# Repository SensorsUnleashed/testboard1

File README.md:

# relayboard
Simple board that will be powered by both mains and a button cell battery.
It is able to:
* Operate a Single Pole Double Throw relay
* Connection for a [Optical Utility Meter LED Pulse Sensor](https://openenergymonitor.org/emon/opticalpulsesensor) from OpenEnergyMonitor
* Has a i2c eeprom
* Can attach to a Sensors Unleashed radio module
* If mains is lost, the relay will release, but the radio will still be operating. This means that messages can still be send even though power is removed.

This board has many uses, but some ideas could be:
Use any installation in the house as input for the system. This device will detect if a button has been toggled, and send messages as instructed. Perhaps turning on/off lamps or plugs in another location in a house.

The board has been ordered from DirtyPCBs 2016-12-05. When tested I will make sure to update this document.

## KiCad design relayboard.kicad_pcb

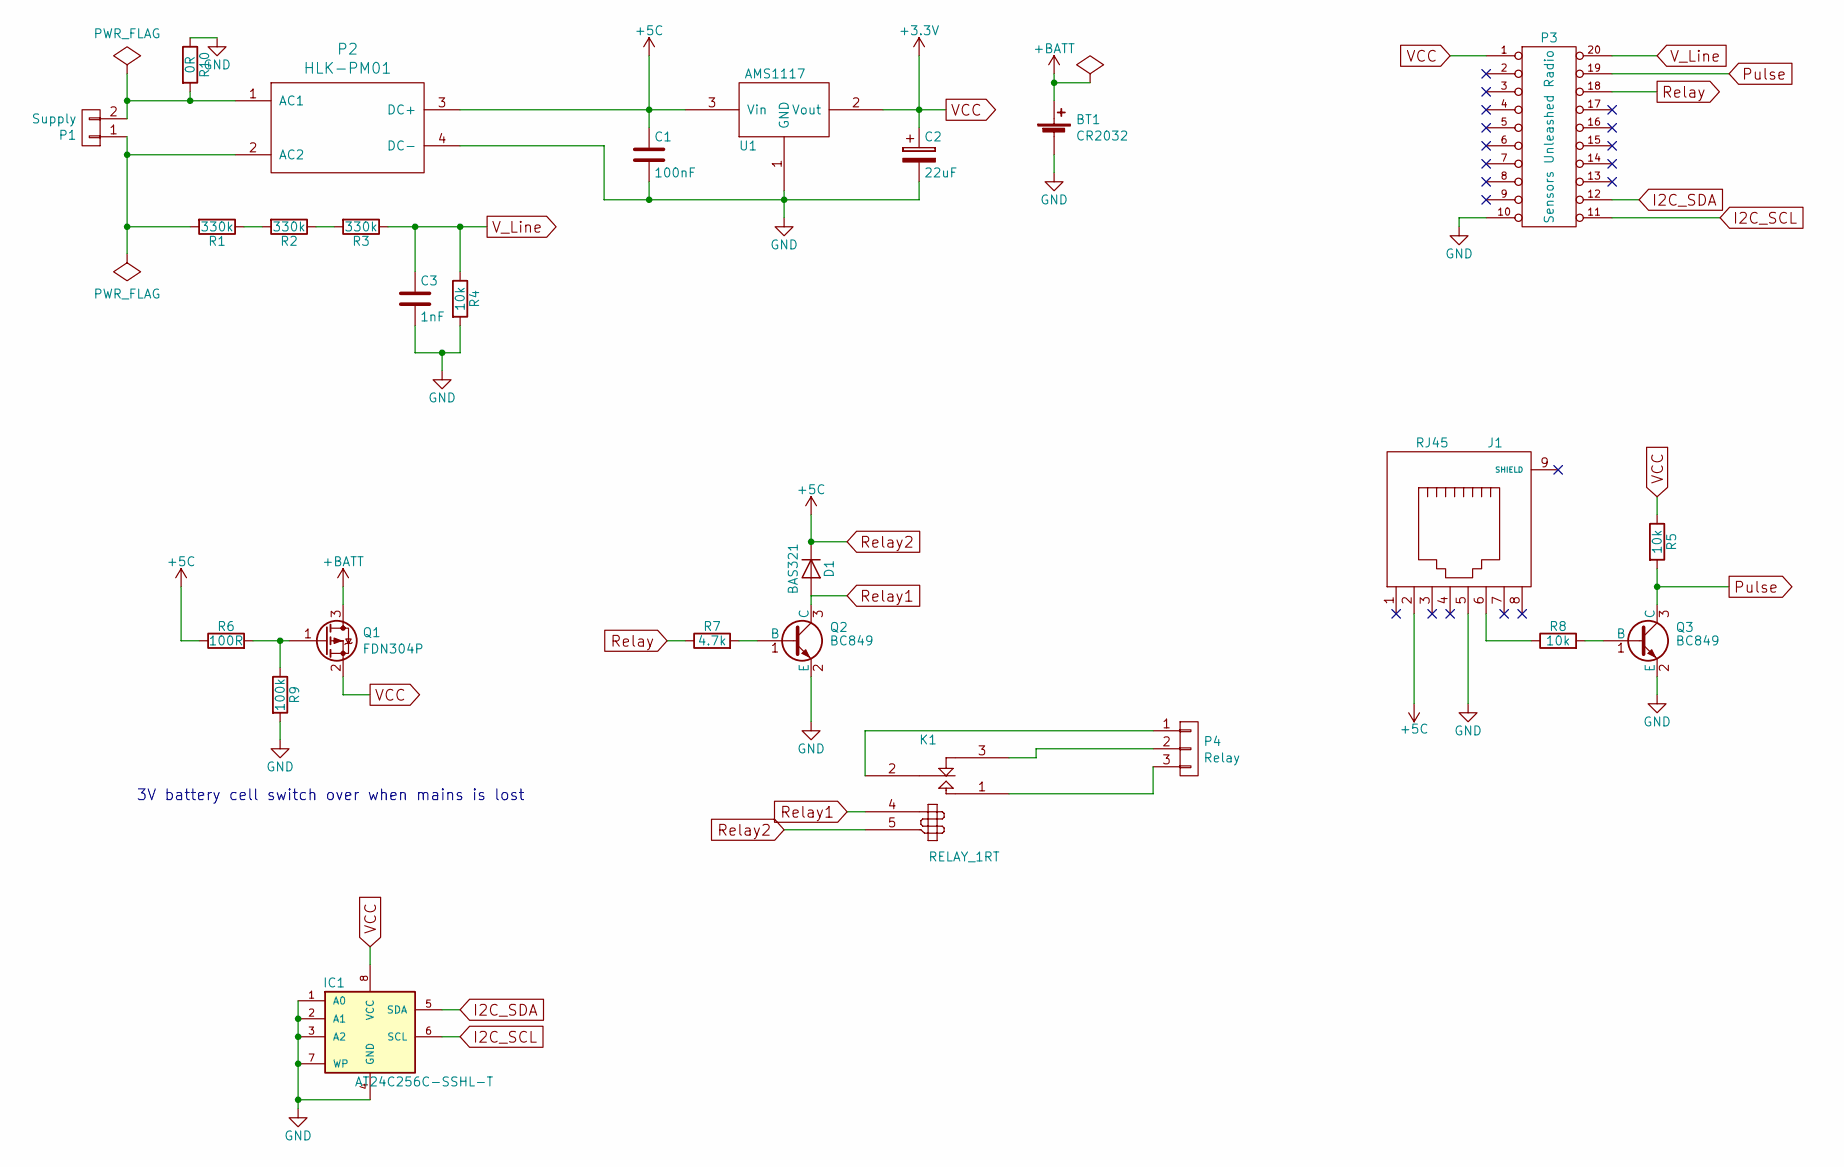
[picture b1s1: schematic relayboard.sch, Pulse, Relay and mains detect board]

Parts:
BT1: CR2032; BATT_CR2032_MPD; Manufacturer Part Number BC2032-F1
C1: 100nF; C_0805
C2: 22uF; C_0805; Manufacturer Part Number F981A226MSA
C3: 1nF; C_0805
D1: BAS321; SOD-323; Manufacturer Part Number BAS321,115
IC1: AT24C256C-SSHL-T; SOIC-8_3.9x4.9mm_Pitch1.27mm
J1: RJ45; RJ45_8
K1: RELAY_1RT; Relay_SRD_XVDC-SL-C_Series
P1: Supply; AK300-2
P2: HLK-PM01
P3: Sensors Unleashed Radio; zb3219PA_radio
P4: Relay; AK300-3
Q1: FDN304P; SSOT-3; Manufacturer Part Number FDN304P
Q2, Q3: BC849; SOT-23
R1, R2, R3: 330k; R_0805
R4, R5, R8: 10k; R_0805
R6: 100R; R_0805
R7: 4.7k; R_0805
R9: 100k; R_0805
R10: 0R; R_0805
U1: AMS1117; SOT-223; Manufacturer Part Number AMS1117-3.3

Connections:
+BATT: BT1.1 (+), Q1.3 (D)
GND: BT1.2 (-), C1.2, C2.2, C3.2, IC1.1 (A0), IC1.2 (A1), IC1.3 (A2), IC1.4 (GND), IC1.7 (WP), J1.5, P2.4 (DC-), P3.10, Q2.2 (E), Q3.2 (E), R4.2, R9.2, R10.1, U1.1 (GND)
I2C_SCL: IC1.6 (SCL), P3.11
I2C_SDA: IC1.5 (SDA), P3.12
unnamed: J1.6, R8.1
unnamed: K1.1 (T1), P4.3
unnamed: K1.2 (C1), P4.1
unnamed: K1.3 (R1), P4.2
unnamed: P1.1, P2.2 (AC2), R1.2
unnamed: P1.2, P2.1 (AC1), R10.2
unnamed: Q1.1 (G), R6.2, R9.1
unnamed: Q2.1 (B), R7.2
unnamed: Q3.1 (B), R8.2
unnamed: R1.1, R2.2
unnamed: R2.1, R3.2
Pulse: P3.19, Q3.3 (C), R5.2
Relay: P3.18, R7.1
Relay1: D1.2 (A), K1.4, Q2.3 (C)
Relay2: C1.1, D1.1 (K), J1.2, K1.5, P2.3 (DC+), R6.1, U1.3 (Vin)
VCC: C2.1, IC1.8 (VCC), P3.1, Q1.2 (S), R5.1, U1.2 (Vout)
V_Line: C3.1, P3.20, R3.1, R4.1

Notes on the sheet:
3V battery cell switch over when mains is lost

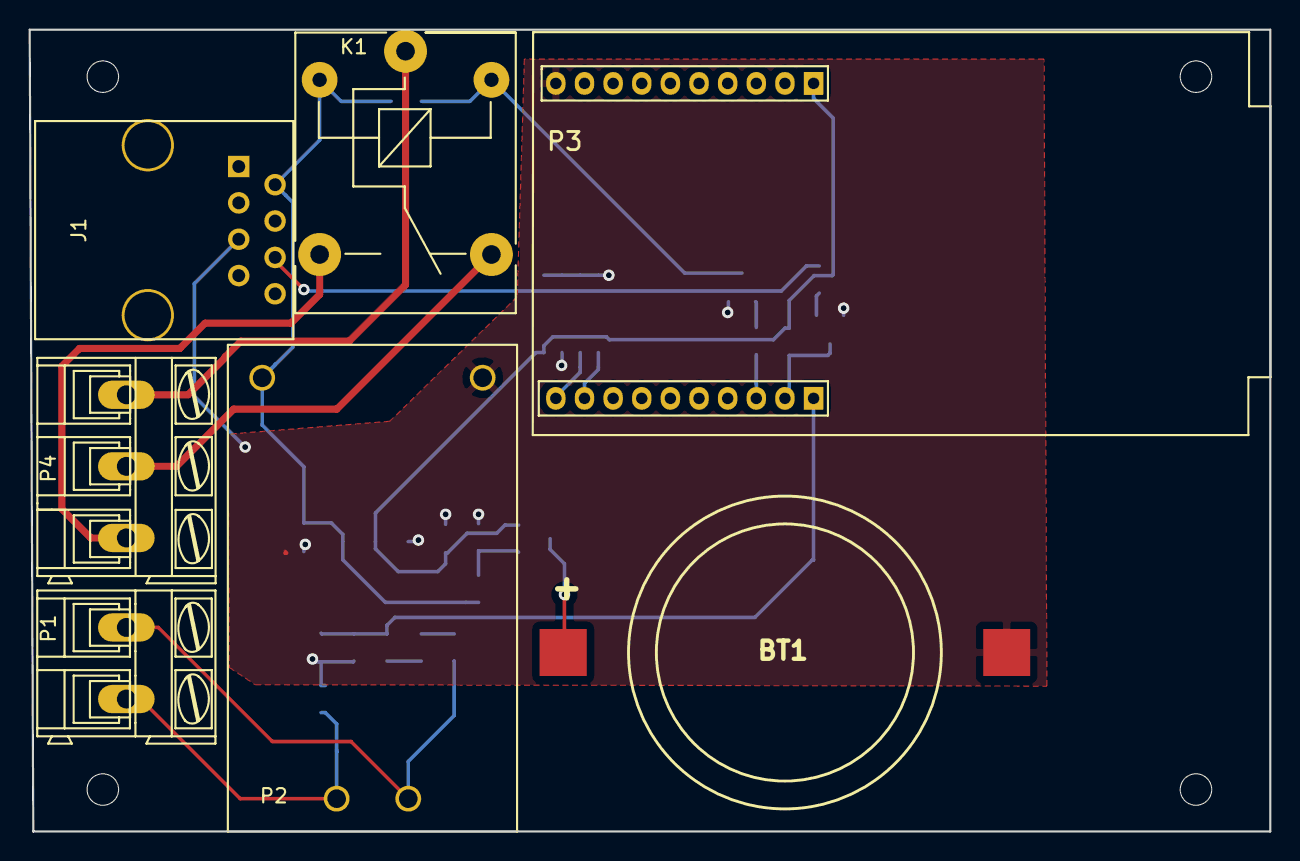
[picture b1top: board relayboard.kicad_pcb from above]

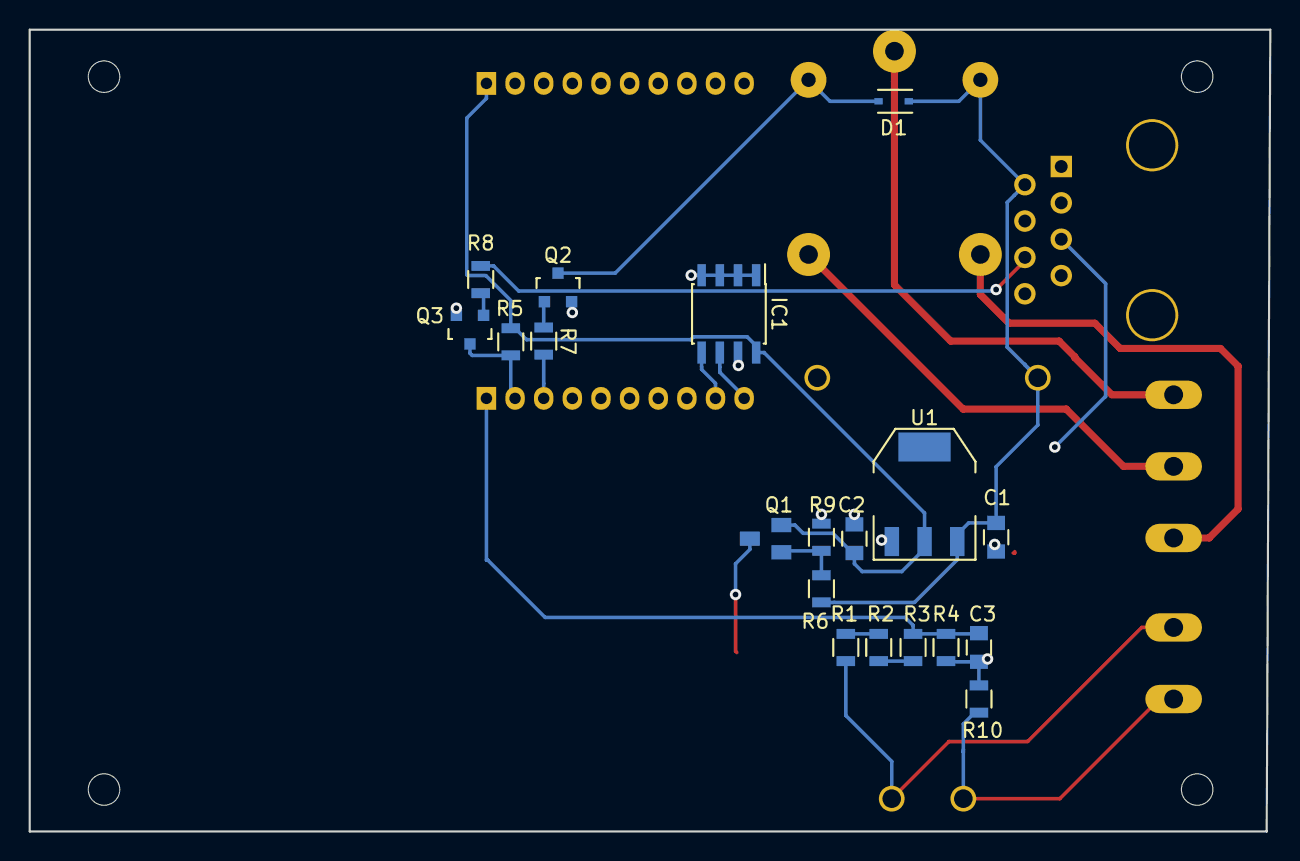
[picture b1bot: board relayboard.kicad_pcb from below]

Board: 2 copper layers, 86.7 x 56.0 mm, 26 parts (19 on the bottom side), 21 nets.

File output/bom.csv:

"Reference"; "Quantity"; "Value"; "Footprint"; "Datasheet"; "Characteristics"; "Package ID"; "Supplier"; "Manufacturer Name"; "Manufacturer Part Number"; "Description"; "Supplier Order number"; "Notes"
"BT1";"1";"CR2032";"SensorsUnleashed:BATT_CR2032_MPD";"http://www.memoryprotectiondevices.com/datasheets/BC2032-F1-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";"Coin, 20.0mm";"smd, Holder (Open)";"Digi Key";"MPD (Memory Protection Devices)";"BC2032-F1";"Coin Cell, Holder";"BC2032-F1-CT-ND";
"C1";"1";"100nF";"Capacitors_SMD:C_0805";"";"25V";"0805";;;;;;
"C2";"1";"22uF";"Capacitors_SMD:C_0805";"http://datasheets.avx.com/F98.pdf";"Tantalum, ESR 4Ohm, 10V, 20%";"0805";"digikey,  478-8649-2-ND";"AVX Corporation";"F981A226MSA";;;
"C3";"1";"1nF";"Capacitors_SMD:C_0805";"";"50V, X7R";"0805";;;;;;
"D1";"1";"BAS321";"Diodes_SMD:SOD-323";"http://www.nxp.com/documents/data_sheet/BAS321.pdf";"Vr=200V, Io=250mA, Vf=1.25V@200mA";"SOD-323";"Digi Key";"NXP Semiconductors";"BAS321,115";"Fast Recovery Rectifiers";"568-6002-1-ND";
"IC1";"1";"AT24C256C-SSHL-T";"Housings_SOIC:SOIC-8_3.9x4.9mm_Pitch1.27mm";"http://www.atmel.com/images/atmel-8568-seeprom-at24c256c-dat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";"256K (32K x 8) eeprom, i2c";"8-SOIC";"Aliexpress";;;;"https://www.aliexpress.com/item/Free-shipping-10pcs-lot-AT24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";
"J1";"1";"RJ45";"Connect:RJ45_8";"";;;;"Optical Utility Meter LED Pulse Sensor";;;;"https://openenergymonitor.org/emon/opticalpulsesensor"
"K1";"1";"RELAY_1RT";"SensorsUnleashed:Relay_SRD_XVDC-SL-C_Series";"";;;"Aliexpress";;;;;
"P1";"1";"Supply";"Connect:AK300-2";""
"P2";"1";"HLK-PM01";"SensorsUnleashed:HLK-PM01";"https://www.aliexpress.com/item/5pcs-TSP-05-replace-HLK-PM01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";"100-240VAC in, 5VDC/3W out";;"Aliexpress";;;;;"Meets CE and UL; written, but not proven!"
"P3";"1";"Sensors Unleashed Radio";"SensorsUnleashed:zb3219PA_radio";""
"P4";"1";"Relay";"Connect:AK300-3";""
"Q1";"1";"FDN304P";"SensorsUnleashed:SSOT-3";"";"20V 2.4A";"SSOT3";;"Fairchild Semiconductor";"FDN304P";"MOSFET P-CH";;
"Q2, Q3";"2";"BC849";"TO_SOT_Packages_SMD:SOT-23";"";;"SOT23";;;;;;
"R1, R2, R3";"3";"330k";"Resistors_SMD:R_0805";"https://industrial.panasonic.com/ww/products/resistors/chip-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";"1%,";"0805";;;;;;
"R10";"1";"0R";"Resistors_SMD:R_0805";"";"1%";"0805";;;;;;
"R4, R5, R8";"3";"10k";"Resistors_SMD:R_0805";"";"1%";"0805";;;;;;
"R6";"1";"100R";"Resistors_SMD:R_0805";"";"1%";"0805";;;;;;
"R7";"1";"4.7k";"Resistors_SMD:R_0805";"";"1%";"0805";;;;;;
"R9";"1";"100k";"Resistors_SMD:R_0805";"";"1%";"0805";;;;;;
"U1";"1";"AMS1117";"TO_SOT_Packages_SMD:SOT-223";"";"Fixed 3.3V, 1A";"SOT-223";;"Advanced Monolithic Systems";"AMS1117-3.3";;;

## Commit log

2016-11-30 Board schematic more or less done. This board can be used, if the production numbers grows, because the custom power supply will only be cheaper then.
2016-12-05 Layout finished. This will be sent to dirty pcb for manufactoring.
2016-12-05 Added gerber files
2016-12-05 Added a better description
